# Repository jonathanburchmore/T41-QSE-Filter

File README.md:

# 5-Band Switching QSE Filter for T41 v11 and Older

## Overview
This project is an automatically switched, 5-band filter board for V11 and older of the T41-EP.  Installed between the QSE and PA boards, these filters reduce harmonics that cause distortion in the PA output that cannot be removed by the output filter board.

This board is compatible with the V11 and older band switch signaling and uses a similar design to the V11 and older filter board.  The 10m filter is always active, and the 80, 40, 20 and 15 meter filters are switched in and out using relays.  With the current filter design, the 10m filter does introduce some insertion loss (see Insertion Loss below).

## Filter Characteristics
The filters used are from the ARRL Handbook, 99th edition, chapter 10.10.4 Optimized Harmonic Transmitting Filters.  They are low-pass filters (not band-pass), and are constructed using SMD components.  Most inductors are Coilcraft 1008CS series (1008 footprint), except for one Murata 0805 inductor in the 10m filter, as there was no 1008 footprint equivalent.

The following filter sweeps include the 10m filter in place so they reflect the loss characteristics described below for the lower bands.

## Insertion Loss
The PCB design is 2-layer and the RF traces are not impedance matched.  Despite this, the board itself shows negligible insertion loss and a relatively flat SWR through 35MHz.

Nevertheless, as can be seen from the filter sweeps above, most of the filters demonstrate approximately 3db of loss.  This is largely due to the presence of the 10m filter, which, as can be seen in the sweep under Filter Characteristics, has a sizeable dip between 5-20MHz.  This characteristic is visible in simulation of the filter so is not due to the construction or part tolerances, and the impact on the other filters has been observed by bypassing the 10m filter.

In the scans below, the 20m filter is shown first with the 10m filter bypassed, and then with it present (note that the trace has a -20dBm offset):

This loss could perhaps be avoided through a different design to the 10m LPF, or by redesigning the board to switch the 10m LPF in only when no other band is active.  In practice, however, I have found little effect from the additional loss and it is easily compensated for through the T41's PA calibration, with no reduction in total power output.

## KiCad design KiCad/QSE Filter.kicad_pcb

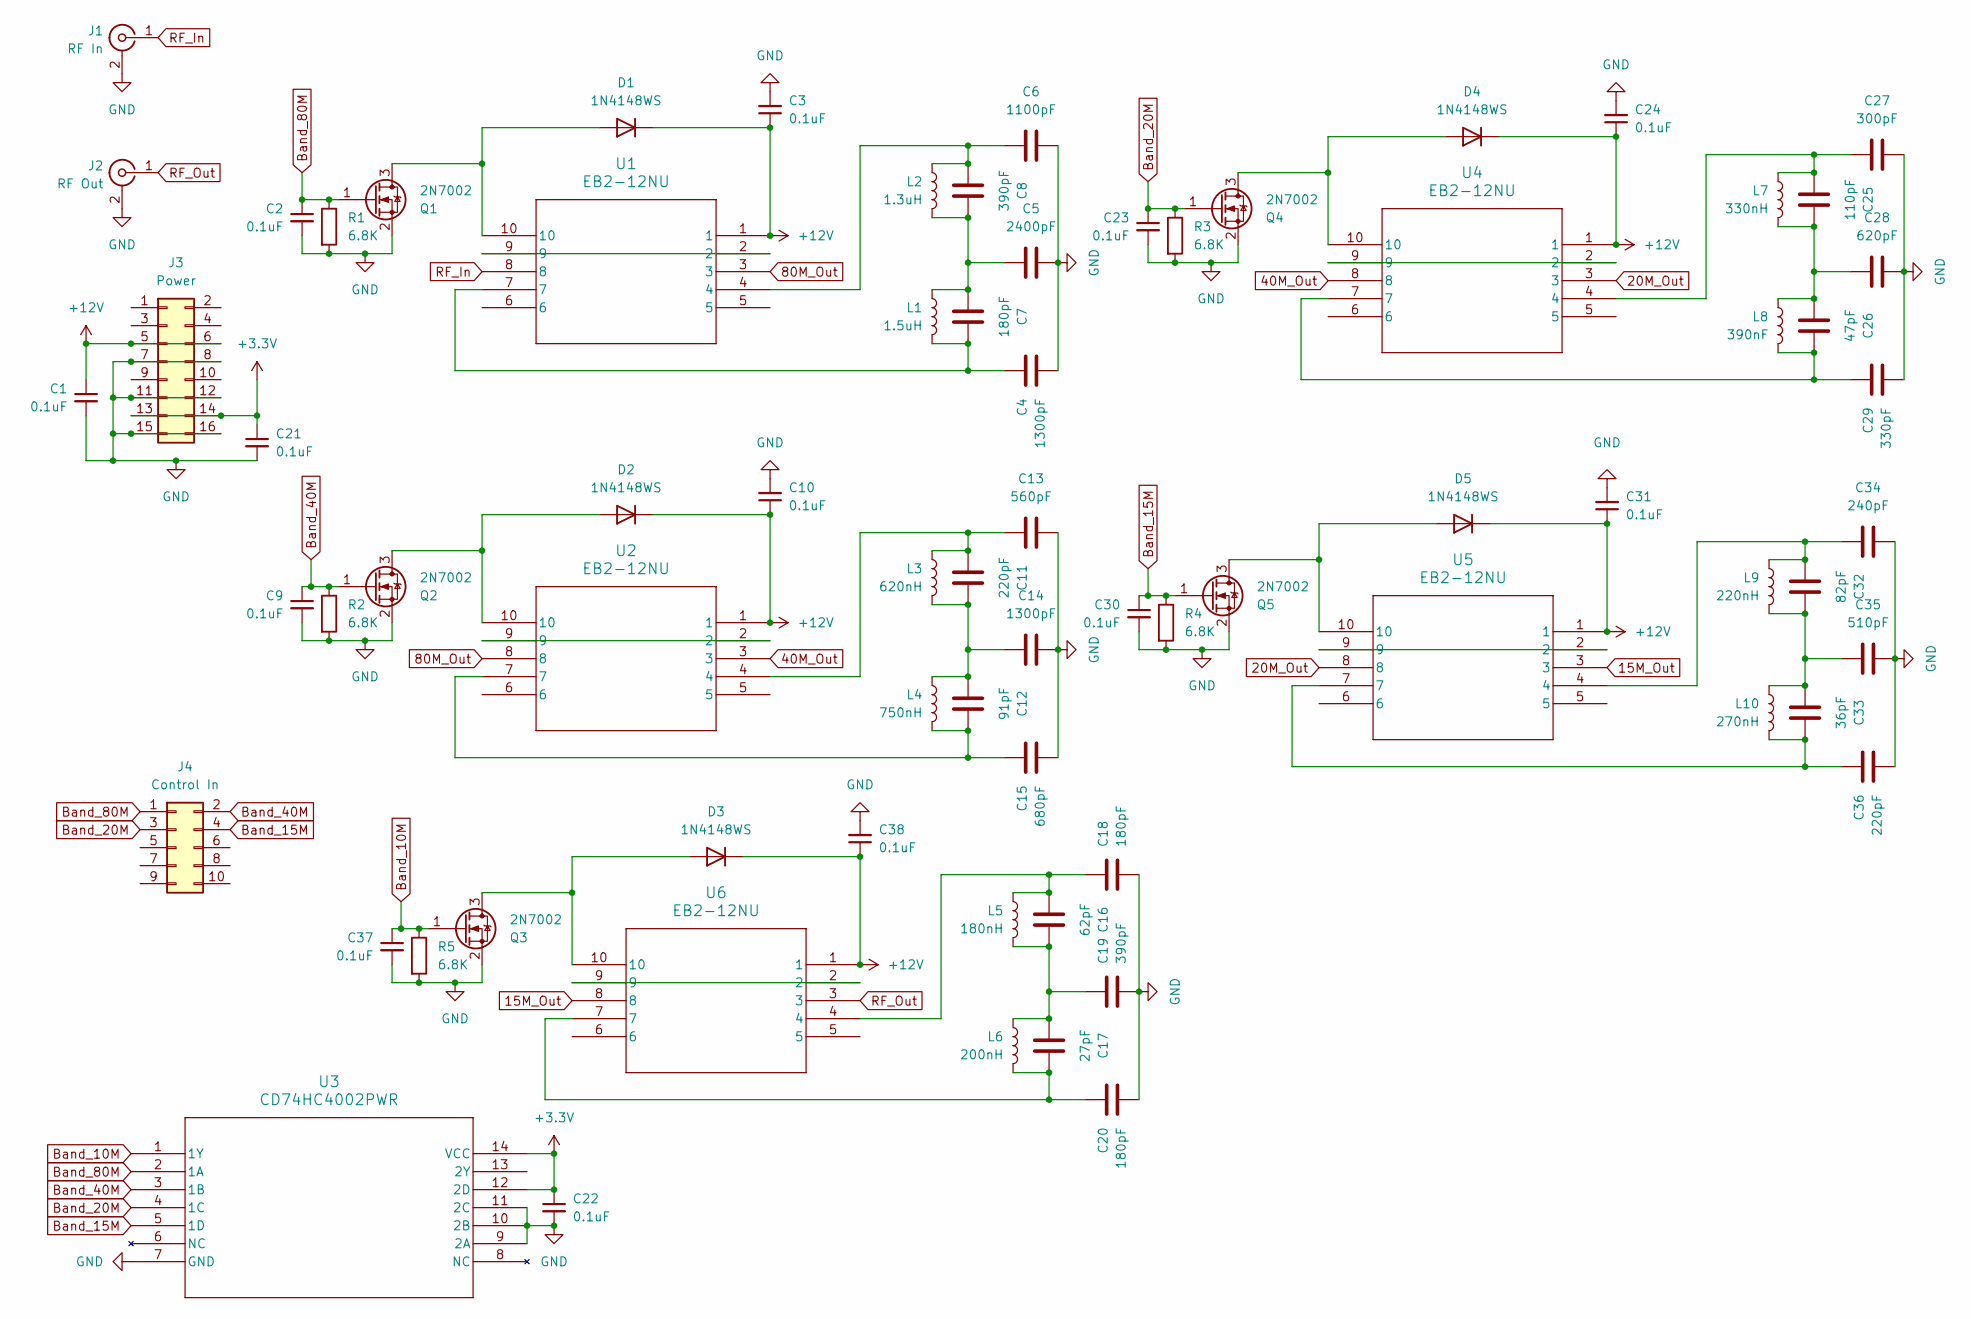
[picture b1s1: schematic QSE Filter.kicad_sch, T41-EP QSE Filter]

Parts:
C1, C2, C3, C9, C10, C21, C22, C23, C24, C30, C31, C37, C38: 0.1uF; C_0805_2012Metric
C4, C14: 1300pF; C_0805_2012Metric
C5: 2400pF; C_0805_2012Metric
C6: 1100pF; C_0805_2012Metric
C7, C18, C20: 180pF; C_0805_2012Metric
C8, C19: 390pF; C_0805_2012Metric
C11, C36: 220pF; C_0805_2012Metric
C12: 91pF; C_0805_2012Metric
C13: 560pF; C_0805_2012Metric
C15: 680pF; C_0805_2012Metric
C16: 62pF; C_0805_2012Metric
C17: 27pF; C_0805_2012Metric
C25: 110pF; C_0805_2012Metric
C26: 47pF; C_0805_2012Metric
C27: 300pF; C_0805_2012Metric
C28: 620pF; C_0805_2012Metric
C29: 330pF; C_0805_2012Metric
C32: 82pF; C_0805_2012Metric
C33: 36pF; C_0805_2012Metric
C34: 240pF; C_0805_2012Metric
C35: 510pF; C_0805_2012Metric
D1, D2, D3, D4, D5: 1N4148WS; D_SOD-323
J1: RF In; CONN_RF2-04A-T-00-50-G_ADM
J2: RF Out; CONN_RF2-04A-T-00-50-G_ADM
J3: Power; IDC-Header_2x08_P2.54mm_Vertical
J4: Control In; IDC-Header_2x05_P2.54mm_Vertical
L1: 1.5uH; IND_1008CS_COC
L2: 1.3uH; IND_1008CS_COC
L3: 620nH; IND_1008CS_COC
L4: 750nH; IND_1008CS_COC
L5: 180nH; IND_1008CS_COC
L6: 200nH; INDC2015X152N
L7: 330nH; IND_1008CS_COC
L8: 390nF; IND_1008CS_COC
L9: 220nH; IND_1008CS_COC
L10: 270nH; IND_1008CS_COC
Q1, Q2, Q3, Q4, Q5: 2N7002; SOT-23
R1, R2, R3, R4, R5: 6.8K; R_0805_2012Metric
U1, U2, U4, U5, U6: EB2-12NU; EB2-12NU_KEM
U3: CD74HC4002PWR; PW14

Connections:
15M_Out: U5.3, U6.8
20M_Out: U4.3, U5.8
40M_Out: U2.3, U4.8
80M_Out: U1.3, U2.8
+3.3V: C21.1, C22.1, J3.13, J3.14, U3.12 (2D), U3.14 (VCC); also elsewhere on the board
+12V: C1.1, C3.1, C10.1, C24.1, C31.1, C38.1, D1.1 (K), D2.1 (K), D3.1 (K), D4.1 (K), D5.1 (K), J3.5, J3.6, U1.1, U2.1, U4.1, U5.1, U6.1
Band_10M: C37.1, Q3.1 (G), R5.1, U3.1 (1Y)
Band_15M: C30.1, J4.4, Q5.1 (G), R4.1, U3.5 (1D)
Band_20M: C23.1, J4.3, Q4.1 (G), R3.1, U3.4 (1C)
Band_40M: C9.1, J4.2, Q2.1 (G), R2.1, U3.3 (1B)
Band_80M: C2.1, J4.1, Q1.1 (G), R1.1, U3.2 (1A)
GND: C1.2, C2.2, C3.2, C4.2, C5.2, C6.2, C9.2, C10.2, C13.2, C14.2, C15.2, C18.2, C19.2, C20.2, C21.2, C22.2, C23.2, C24.2, C27.2, C28.2, C29.2, C30.2, C31.2, C34.2, C35.2, C36.2, C37.2, C38.2, J1.2 (Ext), J1.3 (Ext), J1.4 (Ext), J1.5 (Ext), J2.2 (Ext), J2.3 (Ext), J2.4 (Ext), J2.5 (Ext), J3.7, J3.8, J3.11, J3.12, J3.15, J3.16, Q1.2 (S), Q2.2 (S), Q3.2 (S), Q4.2 (S), Q5.2 (S), R1.2, R2.2, R3.2, R4.2, R5.2, U3.7 (GND), U3.9 (2A), U3.10 (2B), U3.11 (2C); also elsewhere on the board
unnamed: C4.1, C7.1, L1.1, U1.7
unnamed: C5.1, C7.2, C8.1, L1.2, L2.1
unnamed: C6.1, C8.2, L2.2, U1.4
unnamed: C11.1, C12.2, C14.1, L3.1, L4.2
unnamed: C11.2, C13.1, L3.2, U2.4
unnamed: C12.1, C15.1, L4.1, U2.7
unnamed: C16.1, C17.2, C19.1, L5.1, L6.2
unnamed: C16.2, C18.1, L5.2, U6.4
unnamed: C17.1, C20.1, L6.1, U6.7
unnamed: C25.1, C26.2, C28.1, L7.1, L8.2
unnamed: C25.2, C27.1, L7.2, U4.4
unnamed: C26.1, C29.1, L8.1, U4.7
unnamed: C32.1, C33.2, C35.1, L9.1, L10.2
unnamed: C32.2, C34.1, L9.2, U5.4
unnamed: C33.1, C36.1, L10.1, U5.7
unnamed: D1.2 (A), Q1.3 (D), U1.10
unnamed: D2.2 (A), Q2.3 (D), U2.10
unnamed: D3.2 (A), Q3.3 (D), U6.10
unnamed: D4.2 (A), Q4.3 (D), U4.10
unnamed: D5.2 (A), Q5.3 (D), U5.10
unnamed: U1.2, U1.9
unnamed: U2.2, U2.9
unnamed: U4.2, U4.9
unnamed: U5.2, U5.9
unnamed: U6.2, U6.9
RF_In: J1.1 (In), U1.8
RF_Out: J2.1 (In), U6.3

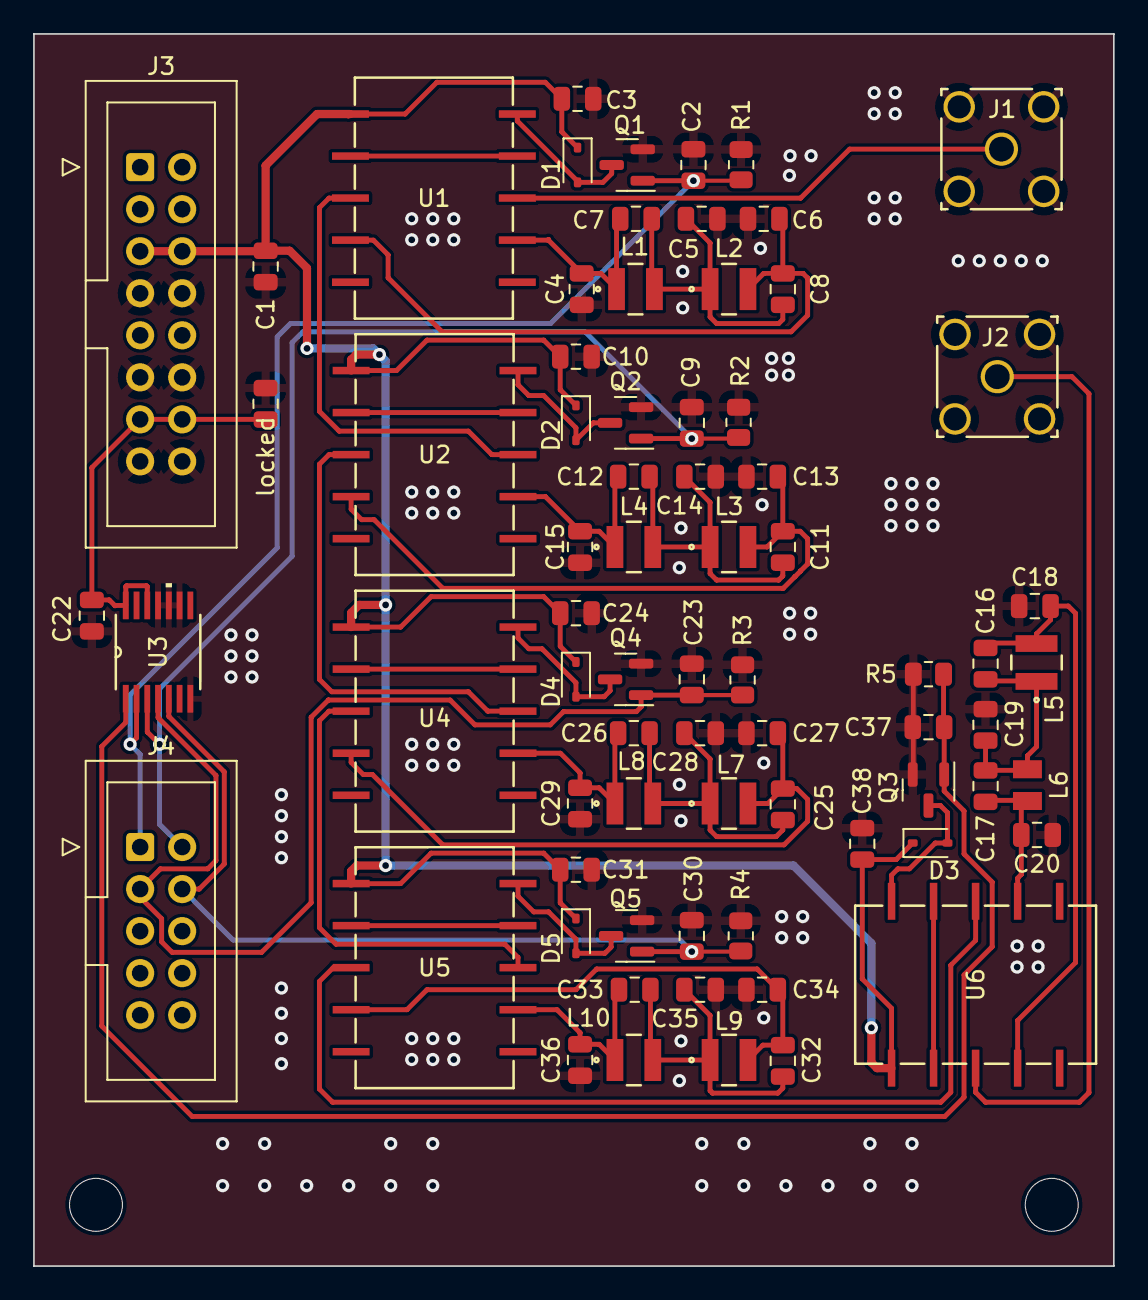
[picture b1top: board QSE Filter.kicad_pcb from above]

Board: 2 copper layers, 65.2 x 74.5 mm, 73 parts (0 on the bottom side), 39 nets.

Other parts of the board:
locked: 0.1uF; C_0805_2012Metric

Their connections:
+3.3V: locked.1; also elsewhere on the board
GND: locked.2; also elsewhere on the board

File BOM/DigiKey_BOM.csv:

Source:,C:\Users\burch\Documents\QSE Filter\QSE Filter.kicad_sch,,,,,,,,,
Date:,1/2/24 21:57,,,,,,,,,
Tool:,Eeschema 7.0.8,,,,,,,,,
Generator:,C:\Program Files\KiCad\7.0\bin\scripting\plugins/bom_csv_grouped_by_value.py,,,,,,,,,
Component Count:,60,,,,,,,,,
,,,,,,,,,,
Collated Components:,,,,,,,,,,
,,,,,,,,,,
Item,Qty,Reference(s),Value,Digikey Part Number,LibPart,Footprint,Datasheet,DNP,Sim.Device,Sim.Pins
1,9,"C1, C2, C3, C9, C10, C23, C24, C30, C31",0.1uF,1276-1003-1-ND,Device:C_Small,Capacitor_SMD:C_0805_2012Metric,~,,,
2,2,"C4, C14",1300pF,490-8290-1-ND,Device:C,Capacitor_SMD:C_0805_2012Metric,~,,,
3,1,C5,2400pF,490-1629-1-ND,Device:C,Capacitor_SMD:C_0805_2012Metric,~,,,
4,1,C6,1100pF,399-14552-1-ND,Device:C,Capacitor_SMD:C_0805_2012Metric,~,,,
5,3,"C7, C18, C20",180pF,399-C0805C181J5GAC7800CT-ND,Device:C,Capacitor_SMD:C_0805_2012Metric,~,,,
6,2,"C8, C19",390pF,399-C0805C391J5GAC7800CT-ND,Device:C,Capacitor_SMD:C_0805_2012Metric,~,,,
7,2,"C11, C36",220pF,399-C0805C221J5GAC7800CT-ND,Device:C,Capacitor_SMD:C_0805_2012Metric,~,,,
8,1,C12,91pF,311-4244-1-ND,Device:C,Capacitor_SMD:C_0805_2012Metric,~,,,
9,1,C13,560pF,311-1120-1-ND,Device:C,Capacitor_SMD:C_0805_2012Metric,~,,,
10,1,C15,680pF,311-1121-1-ND,Device:C,Capacitor_SMD:C_0805_2012Metric,~,,,
11,1,C16,62pF,311-4241-1-ND,Device:C,Capacitor_SMD:C_0805_2012Metric,~,,,
12,1,C17,27pF,311-1104-1-ND,Device:C,Capacitor_SMD:C_0805_2012Metric,~,,,
13,1,C25,110pF,399-15438-1-ND,Device:C,Capacitor_SMD:C_0805_2012Metric,~,,,
14,1,C26,47pF,399-C0805C470J5GAC7210CT-ND,Device:C,Capacitor_SMD:C_0805_2012Metric,~,,,
15,1,C27,300pF,490-12550-2-ND,Device:C,Capacitor_SMD:C_0805_2012Metric,~,,,
16,1,C28,620pF,311-4242-1-ND,Device:C,Capacitor_SMD:C_0805_2012Metric,~,,,
17,1,C29,330pF,399-C0805C331J5GAC7800CT-ND,Device:C,Capacitor_SMD:C_0805_2012Metric,~,,,
18,1,C32,82pF,311-1110-1-ND,Device:C,Capacitor_SMD:C_0805_2012Metric,~,,,
19,1,C33,36pF,311-4236-1-ND,Device:C,Capacitor_SMD:C_0805_2012Metric,~,,,
20,1,C34,240pF,311-4232-1-ND,Device:C,Capacitor_SMD:C_0805_2012Metric,~,,,
21,1,C35,510pF,311-4240-1-ND,Device:C,Capacitor_SMD:C_0805_2012Metric,~,,,
22,4,"D1, D2, D4, D5",1N4148WS,1N4148WSF-7DICT-ND,Diode:1N4148WS,Diode_SMD:D_SOD-323,https://www.vishay.com/docs/85751/1n4148ws.pdf,,D,1=K 2=A
23,1,J1,RF In,2057-RF2-04A-T-00-50-G-ND,Connector:Conn_Coaxial,Connector_Coaxial:SMA_Amphenol_132134_Vertical, ~,,,
24,1,J2,RF Out,2057-RF2-04A-T-00-50-G-ND,Connector:Conn_Coaxial,Connector_Coaxial:SMA_Amphenol_132134_Vertical, ~,,,
25,1,J3,Power,1175-1611-ND,Connector_Generic:Conn_02x08_Odd_Even,Connector_IDC:IDC-Header_2x08_P2.54mm_Vertical,~,,,
26,1,J4,Control In,3020-10-0100-00,Connector_Generic:Conn_02x05_Odd_Even,Connector_IDC:IDC-Header_2x05_P2.54mm_Vertical,~,,,
27,1,L1,1.5uH,2457-1008CS-152XJRC-ND,Device:L,IND_1008CS_COC:IND_1008CS_COC,~,,,
28,1,L2,1.3uH,2457-1008CS-132XJRC-ND,Device:L,IND_1008CS_COC:IND_1008CS_COC,~,,,
29,1,L3,620nH,2457-1008CS-621XJRC-ND,Device:L,IND_1008CS_COC:IND_1008CS_COC,~,,,
30,1,L4,750nH,2457-1008CS-751XJRC-ND,Device:L,IND_1008CS_COC:IND_1008CS_COC,~,,,
31,1,L5,180nH,2457-1008CS-181XJRC-ND,Device:L,IND_1008CS_COC:IND_1008CS_COC,~,,,
31,1,L6,200nH,490-16070-1-ND,Device:L,IND_1008CS_COC:IND_1008CS_COC,~,,,
32,1,L7,330nH,2457-1008CS-331XJRC-ND,Device:L,IND_1008CS_COC:IND_1008CS_COC,~,,,
33,1,L8,390nF,2457-1008CS-391XJRC-ND,Device:L,IND_1008CS_COC:IND_1008CS_COC,~,,,
34,1,L9,220nH,2457-1008CS-221XJRC-ND,Device:L,IND_1008CS_COC:IND_1008CS_COC,~,,,
34,1,L10,270nH,2457-1008CS-271XJRC-ND,Device:L,IND_1008CS_COC:IND_1008CS_COC,~,,,
35,4,"Q1, Q2, Q4, Q5",2N7002,1727-4789-1-ND,Transistor_FET:2N7002,Package_TO_SOT_SMD:SOT-23,https://www.onsemi.com/pub/Collateral/NDS7002A-D.PDF,,,
36,4,"U1, U2, U4, U5",EB2-12NU,EB2-12NU-ND,Kemet EB2-12NU-L:EB2-12NU,Kemet_EB2:EB2-12NU_KEM,EB2-12NU,,,
37,4,"R1,R2,R3,R4",6.8K,RMCF0805JT6K80CT-ND,,,,,,

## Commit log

2024-01-15 Initial commit. V1 Gerbers, V2 KiCad, updated/corrected DigiKey BOM.
2024-01-15 Current schematic
2024-01-15 Updated images with normalized TG output and 0 dBm reference (less confusing)
2024-01-15 Photo of assembled v1 board
2024-01-15 Renamed
2024-01-15 Renamed files to eliminate spaces (necessary for links within README.md)
2024-01-15 Smaller image
2024-01-15 20m insertion loss sweeps
2024-01-15 Create LICENSE
2024-01-16 Eliminate acute angles/acid traps in various traces Move C1 slightly
2024-01-16 Move C1 silkscreen
2024-01-16 Created project symbol and footprint libraries
2024-01-16 Corrected RF connector symbol so KiCad will stop disconnecting pins 3, 4, 5, by creating a stack of invisible pins Updated all footprints and symbols to pull from the QSE Filter library
2024-01-16 Adding to git
2024-01-16 Added CD74HC4002PWR symbol and PW14 footprint for quad-NOR gate
2024-01-18 Added switched 10m LPF using a 4-input NOR gate to control the 10m filter relay
2024-01-18 Assigned C21 and C22 footprints Corrected RF out pin on U6
2024-01-18 Ground C38 pin 2
2024-01-18 Initial layout with switched 10m LPF. Passes all DRC however has some islands and has a trace possibly too close to the edge of the PCB.
2024-01-18 Adding PW14.kicad_mod
2024-01-19 Resolved ground pour islands, moved RF out trace off the extreme right edge of the PCB, other minor layout changes.
2024-01-19 Updated schematic revision to 2, updated Schematic.pdf
2024-01-22 Gerber update
2024-02-12 Updated LPF images from V2 PCB with switched 10m LPF
